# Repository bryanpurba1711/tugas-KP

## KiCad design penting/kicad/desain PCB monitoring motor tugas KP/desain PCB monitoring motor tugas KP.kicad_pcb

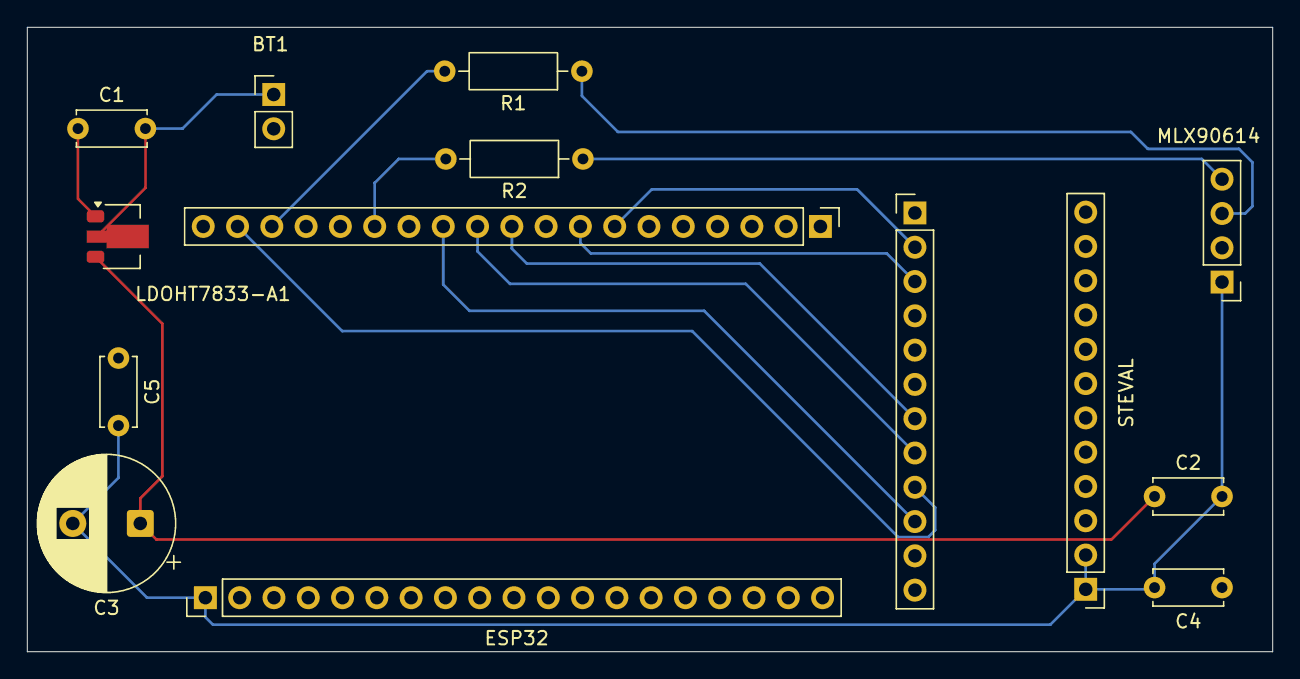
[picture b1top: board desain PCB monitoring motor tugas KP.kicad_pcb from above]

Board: 2 copper layers, 92.2 x 46.2 mm, 14 parts (0 on the bottom side), 14 nets.

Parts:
BT1: Battery_Cell; PinHeader_1x02_P2.54mm_Vertical
C1, C2, C5: 10 uF; C_Disc_D5.0mm_W2.5mm_P5.00mm
C3: 1 F; CP_Radial_D10.0mm_P5.00mm
C4: 100 nF; C_Disc_D5.0mm_W2.5mm_P5.00mm
ESP32: Conn_01x19; PinHeader_1x19_P2.54mm_Vertical
J2: Conn_01x19; PinHeader_1x19_P2.54mm_Vertical
J6: Conn_01x12; PinHeader_1x12_P2.54mm_Vertical
LDOHT7833-A1: MCP1700x-330xxMB; SOT-89-3
MLX90614: Conn_01x04; PinHeader_1x04_P2.54mm_Vertical
R1, R2: 4.7K; R_Axial_DIN0207_L6.3mm_D2.5mm_P10.16mm_Horizontal
STEVAL: Conn_01x12; PinHeader_1x12_P2.54mm_Vertical

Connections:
/3V3: C2.2, C3.2, C4.2, C5.2, ESP32.1, MLX90614.1, STEVAL.1, STEVAL.2
/4: J2.7, J6.2
/5: J2.10, J6.7
/16: J2.8, J6.3
/18: J2.11, J6.8
/19: J2.12, J6.10
/21: J2.14, R2.2
/22: J2.17, R1.2
/23: J2.18, J6.9
GND: BT1.2 (-), C1.1, C4.1, C5.1, ESP32.14, J2.13, J2.19, J6.1, LDOHT7833-A1.1 (GND), MLX90614.2
unnamed: BT1.1 (+), C1.2, LDOHT7833-A1.2 (VI)
unnamed: C2.1, C3.1, LDOHT7833-A1.3 (VO)
unnamed: MLX90614.3, R1.1
unnamed: MLX90614.4, R2.1
